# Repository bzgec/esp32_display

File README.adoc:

= MQTT display HW
:toc:
:sectnums:
:sectnumlevels: 4

* Current version: *0.1*
* link:./CHANGELOG.adoc[Changelog]

'''

MQTT display using:

* ESP32
* ILI9341 display

[link="./Res/pic/display_mqtt.jpg"]
.Example
image::./Res/pic/display_mqtt.jpg[alt="display_mqtt", height="250px", align="center"]

== PCB:

=== v0.1

[link="./Res/pic/hw_v0.1_bottom_real.jpg"]
.HW v0.1
image::./Res/pic/hw_v0.1_bottom_real.jpg[alt="hw_v0.1_bottom_real", height="300px", align="center"]

== Automated exporting
=== Installation
==== KiBot
link:https://github.com/INTI-CMNB/kibot#installation-using-pip[Installation]:

* `pip install --no-compile kibot`
(on Windows you probably need to install it in `KiCad Command Prompt`)

* On Arch Linux you can install it with: `paru -S kibot-git`
** You may need to install `pcbdraw-git` in case of
`module 'pcbnew' has no attribute 'PLOTTEXTMODE_STROKE'` error
(try to run `pcbnew --version` to be sure that program runs correctly)
** You also may need to install `imagemagick`: `sudo pacman -S imagemagick`
** You also may need to install few `pip` packages: `pip install mistune pybars3 wand`

==== recordmydesktop
* Needed only if running `kibot -vvv`
* Arch Linux: `sudo pacman -S recordmydesktop`

== TODO
* [ ] Fix silkscreen for programming connector (TX and RX are replaced, also the same for IO0 and RST)
* [ ] Remove Display module SD card slot - that way display can seat lower
  (whole PCB if then thinner)

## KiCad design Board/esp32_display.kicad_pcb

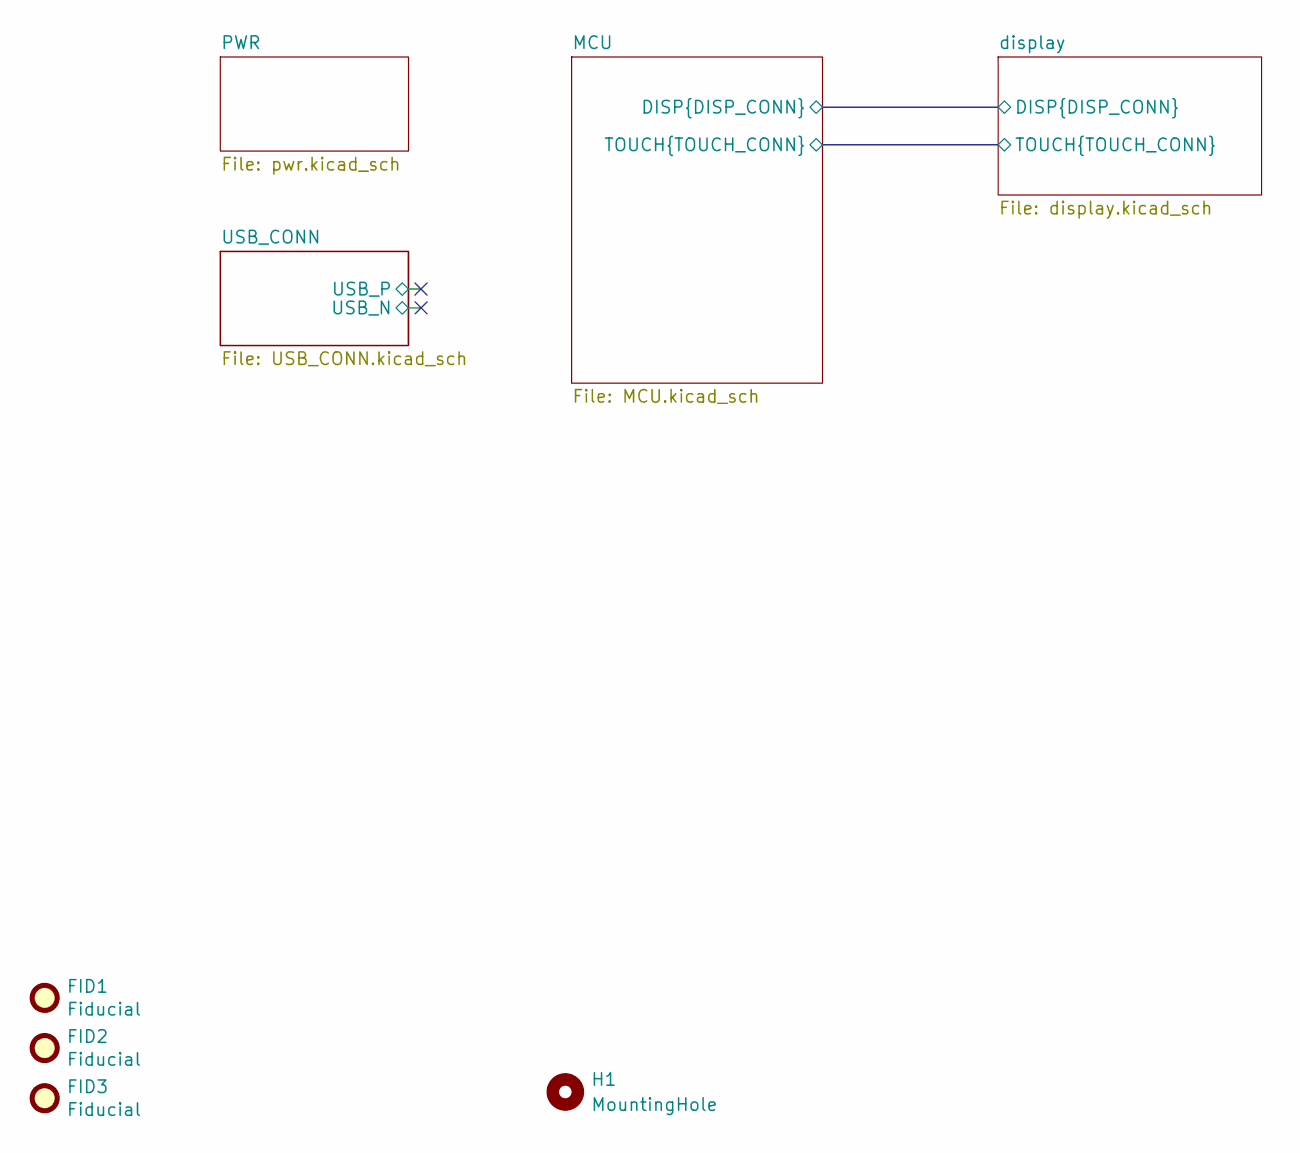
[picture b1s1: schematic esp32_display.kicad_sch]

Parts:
FID1, FID2, FID3: Fiducial; Fiducial_0.5mm_Mask1mm
H1: MountingHole; MountingHole_3.2mm_M3_ISO14580

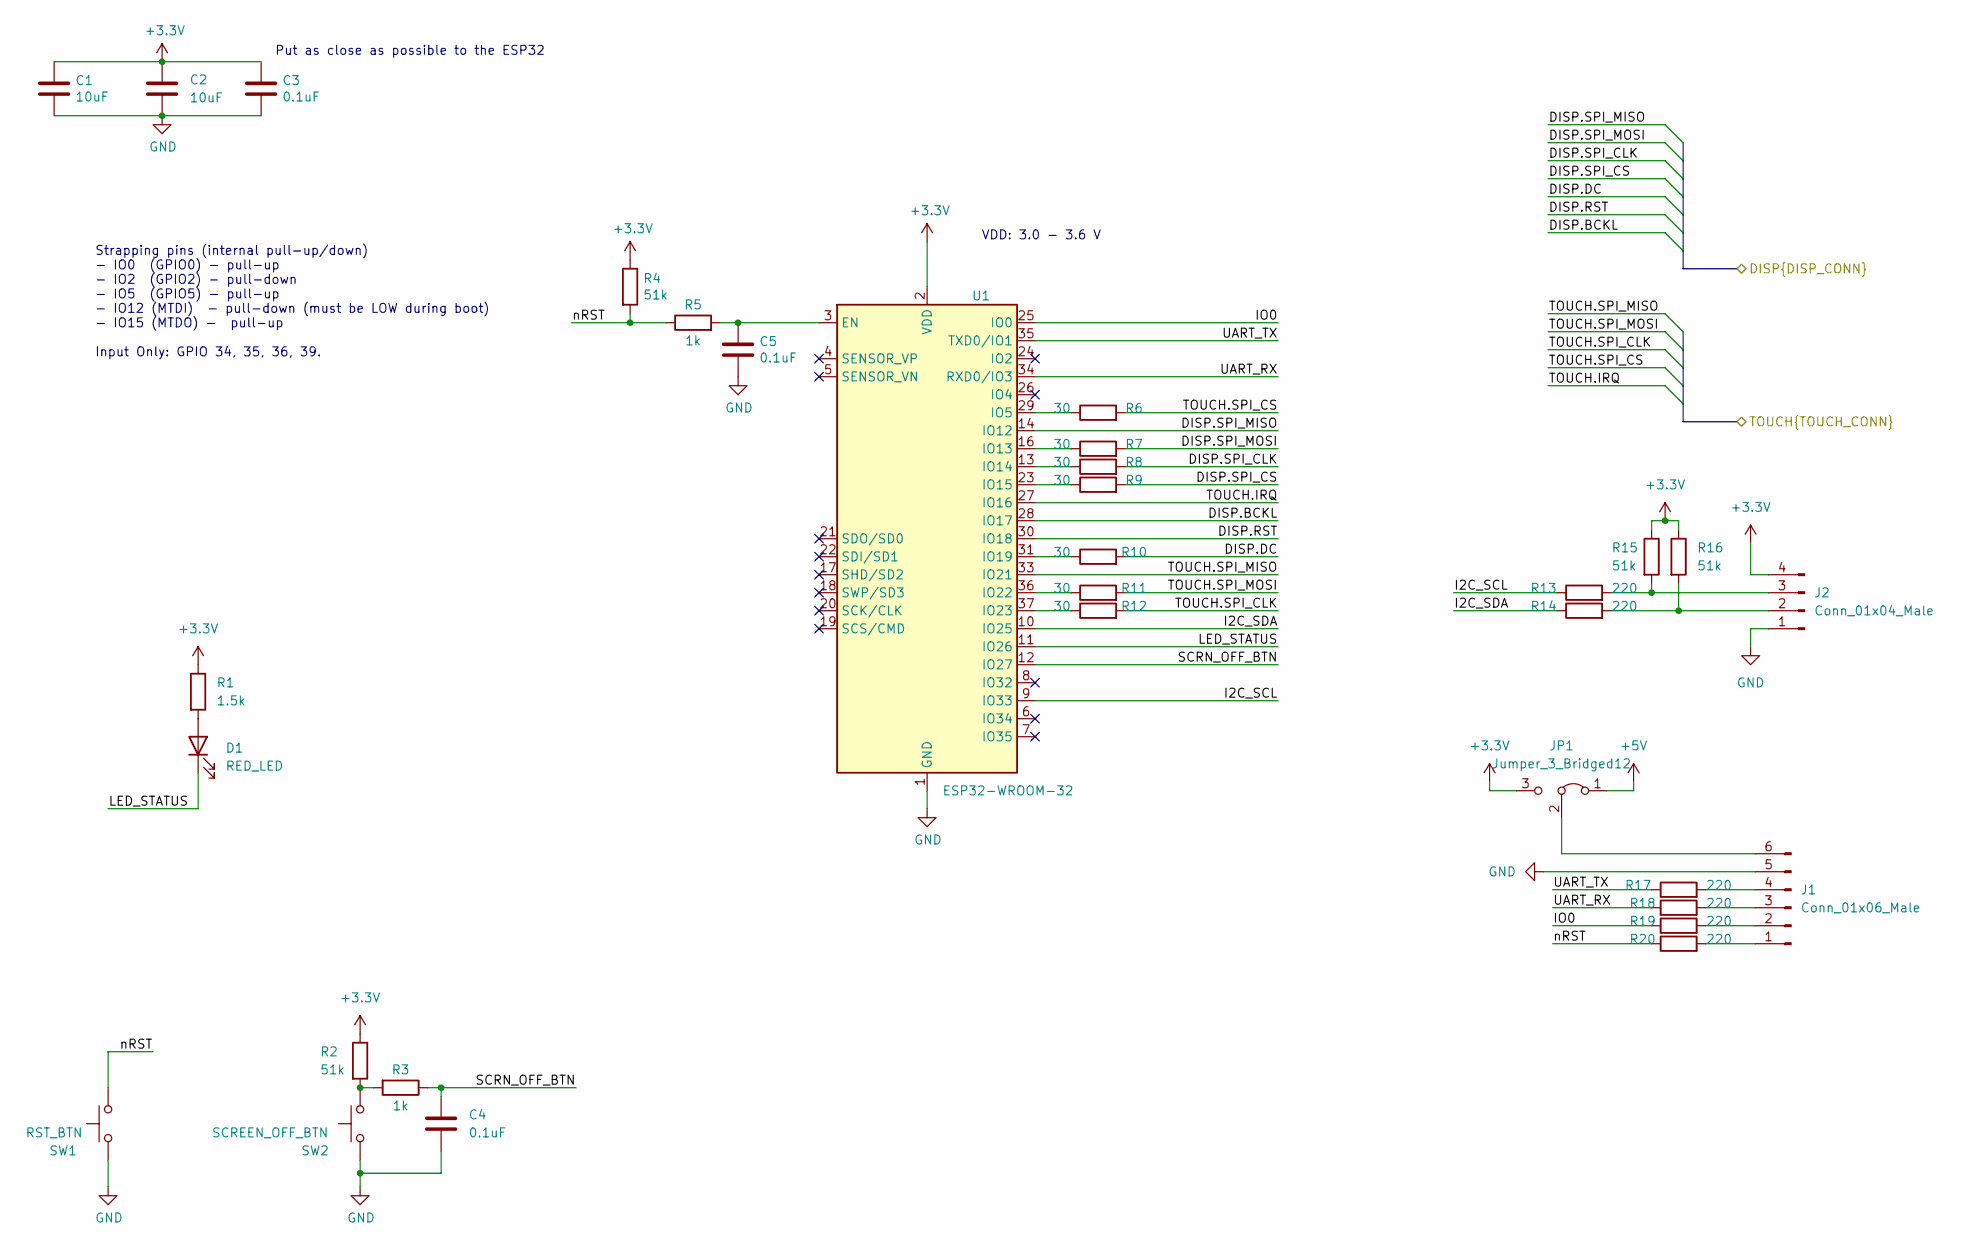
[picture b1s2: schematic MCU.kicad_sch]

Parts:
C1, C2: 10uF; C_0603_1608Metric_Pad1.08x0.95mm_HandSolder
C3, C4, C5: 0.1uF; C_0603_1608Metric_Pad1.08x0.95mm_HandSolder
D1: RED_LED; D_0603_1608Metric_Pad1.05x0.95mm_HandSolder
J1: Conn_01x06_Male; PinHeader_1x06_P2.54mm_Horizontal
J2: Conn_01x04_Male; PinHeader_1x04_P2.54mm_Horizontal
JP1: Jumper_3_Bridged12; SolderJumper-3_P1.3mm_Bridged12_RoundedPad1.0x1.5mm
R1: 1.5k; R_0603_1608Metric_Pad0.98x0.95mm_HandSolder
R2, R4, R15, R16: 51k; R_0603_1608Metric_Pad0.98x0.95mm_HandSolder
R3, R5: 1k; R_0603_1608Metric_Pad0.98x0.95mm_HandSolder
R6, R7, R8, R9, R10, R11, R12: 30; R_0603_1608Metric_Pad0.98x0.95mm_HandSolder
R13, R14, R17, R18, R19, R20: 220; R_0603_1608Metric_Pad0.98x0.95mm_HandSolder
SW1: RST_BTN; SW_Tactile_SPST_Angled_PTS645Vx83-2LFS
SW2: SCREEN_OFF_BTN; SW_Tactile_SPST_Angled_PTS645Vx83-2LFS
U1: ESP32-WROOM-32

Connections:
+3V3: C1.1, C2.1, C3.1, J2.4, JP1.3 (B), R1.1, R2.1, R4.1, R15.1, R16.1, U1.2 (VDD); also elsewhere on the board
+5V: JP1.1 (A); also elsewhere on the board
/MCU/DISP.BCKL: U1.28 (IO17); also elsewhere on the board
/MCU/DISP.DC: R10.2; also elsewhere on the board
/MCU/DISP.RST: U1.30 (IO18); also elsewhere on the board
/MCU/DISP.SPI_CLK: R8.2; also elsewhere on the board
/MCU/DISP.SPI_CS: R9.2; also elsewhere on the board
/MCU/DISP.SPI_MISO: U1.14 (IO12); also elsewhere on the board
/MCU/DISP.SPI_MOSI: R7.2; also elsewhere on the board
/MCU/I2C_SCL: R13.1, U1.9 (IO33)
/MCU/I2C_SDA: R14.1, U1.10 (IO25)
/MCU/IO0: R19.1, U1.25 (IO0)
/MCU/LED_STATUS: D1.1 (K), U1.11 (IO26)
/MCU/SCRN_OFF_BTN: C4.1, R3.1, U1.12 (IO27)
/MCU/TOUCH.IRQ: U1.27 (IO16); also elsewhere on the board
/MCU/TOUCH.SPI_CLK: R12.2; also elsewhere on the board
/MCU/TOUCH.SPI_CS: R6.2; also elsewhere on the board
/MCU/TOUCH.SPI_MISO: U1.33 (IO21); also elsewhere on the board
/MCU/TOUCH.SPI_MOSI: R11.2; also elsewhere on the board
/MCU/UART_RX: R18.1, U1.34 (RXD0/IO3)
/MCU/UART_TX: R17.1, U1.35 (TXD0/IO1)
/MCU/nRST: R4.2, R5.1, R20.1, SW1.1
GND: C1.2, C2.2, C3.2, C4.2, C5.2, J1.5, J2.1, SW1.2, SW2.2, U1.1 (GND), U1.15 (GND), U1.38 (GND), U1.39 (GND); also elsewhere on the board
unnamed: C5.1, R5.2, U1.3 (EN)
unnamed: D1.2 (A), R1.2
unnamed: J1.1, R20.2
unnamed: J1.2, R19.2
unnamed: J1.3, R18.2
unnamed: J1.4, R17.2
unnamed: J1.6, JP1.2 (C)
unnamed: J2.2, R14.2, R16.2
unnamed: J2.3, R13.2, R15.2
unnamed: R2.2, R3.2, SW2.1
unnamed: R6.1, U1.29 (IO5)
unnamed: R7.1, U1.16 (IO13)
unnamed: R8.1, U1.13 (IO14)
unnamed: R9.1, U1.23 (IO15)
unnamed: R10.1, U1.31 (IO19)
unnamed: R11.1, U1.36 (IO22)
unnamed: R12.1, U1.37 (IO23)

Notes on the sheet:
Put as close as possible to the ESP32
Strapping pins (internal pull-up/down) - IO0 (GPIO0) - pull-up - IO2 (GPIO2) - pull-down - IO5 (GPIO5) - pull-up - IO12 (MTDI) - pull-down (must be LOW during boot) - IO15 (MTDO) - pull-up Input Only: GPIO 34, 35, 36, 39.
VDD: 3.0 - 3.6 V

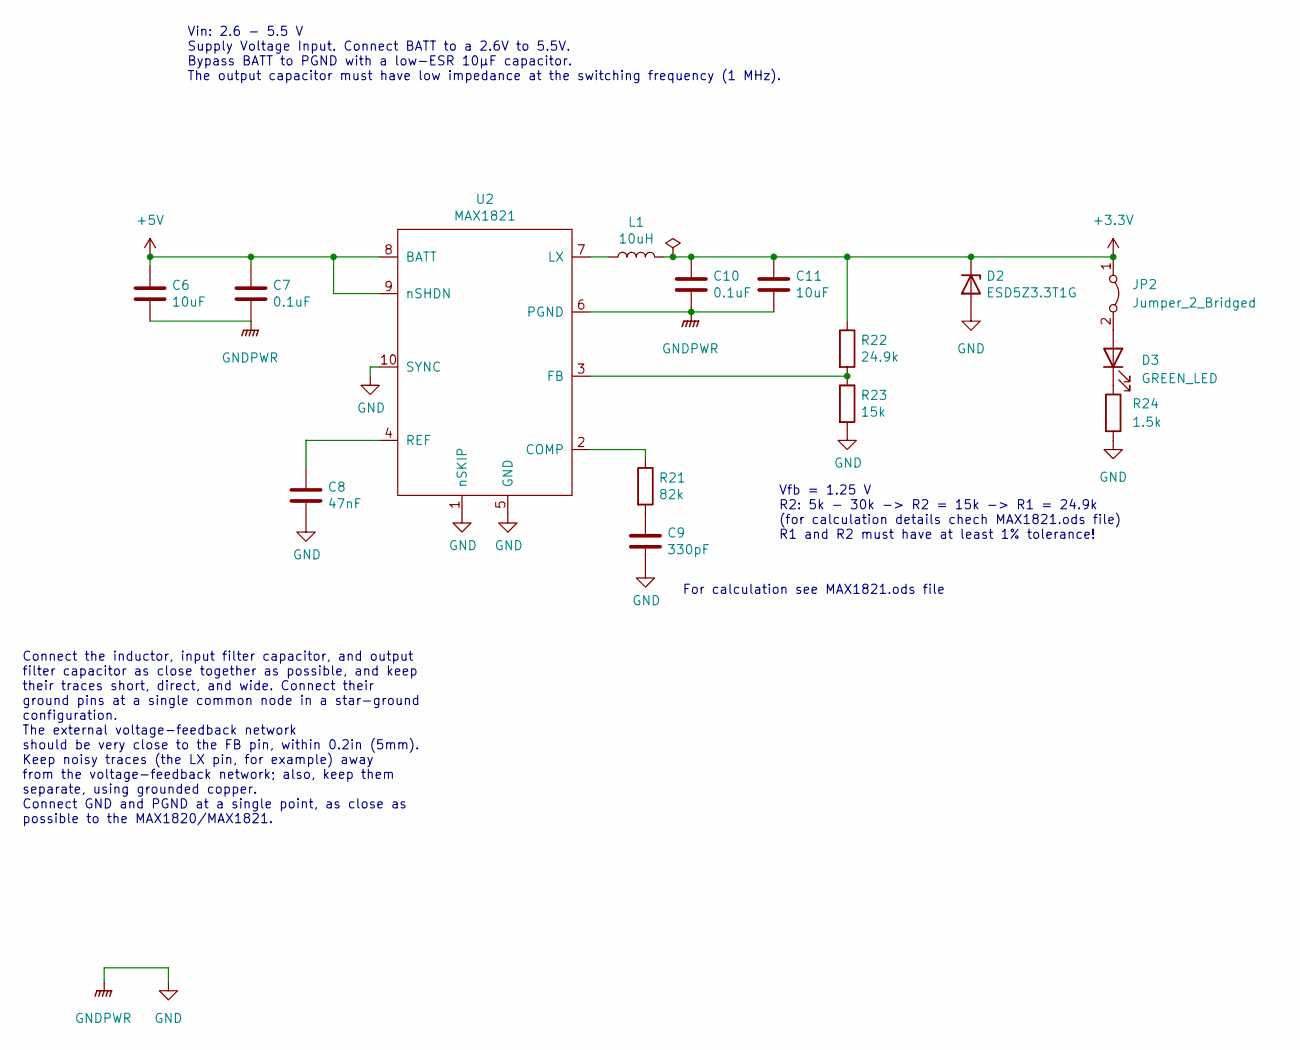
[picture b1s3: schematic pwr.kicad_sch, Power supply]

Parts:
C6, C11: 10uF; C_0603_1608Metric_Pad1.08x0.95mm_HandSolder
C7, C10: 0.1uF; C_0603_1608Metric_Pad1.08x0.95mm_HandSolder
C8: 47nF; C_0603_1608Metric_Pad1.08x0.95mm_HandSolder
C9: 330pF; C_0603_1608Metric_Pad1.08x0.95mm_HandSolder
D2: ESD5Z3.3T1G; D_SOD-523
D3: GREEN_LED; D_0603_1608Metric_Pad1.05x0.95mm_HandSolder
JP2: Jumper_2_Bridged; PinHeader_1x02_P2.54mm_Horizontal
L1: 10uH; NR6028T100M
R21: 82k; R_0603_1608Metric_Pad0.98x0.95mm_HandSolder
R22: 24.9k; R_0603_1608Metric_Pad0.98x0.95mm_HandSolder
R23: 15k; R_0603_1608Metric_Pad0.98x0.95mm_HandSolder
R24: 1.5k; R_0603_1608Metric_Pad0.98x0.95mm_HandSolder
U2: MAX1821; MAX1821EUB+

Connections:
+3V3: C10.1, C11.1, D2.1 (K), JP2.1 (A), L1.2, R22.1; also elsewhere on the board
+5V: C6.1, C7.1, U2.8 (BATT), U2.9 (nSHDN); also elsewhere on the board
GND: C6.2, C7.2, C8.2, C9.2, C10.2, C11.2, D2.2 (A), R23.2, R24.2, U2.1 (nSKIP), U2.5 (GND), U2.6 (PGND), U2.10 (SYNC); also elsewhere on the board
unnamed: C8.1, U2.4 (REF)
unnamed: C9.1, R21.2
unnamed: D3.1 (K), R24.1
unnamed: D3.2 (A), JP2.2 (B)
unnamed: L1.1, U2.7 (LX)
unnamed: R21.1, U2.2 (COMP)
unnamed: R22.2, R23.1, U2.3 (FB)

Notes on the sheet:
Vfb = 1.25 V R2: 5k - 30k -> R2 = 15k -> R1 = 24.9k (for calculation details chech MAX1821.ods file) R1 and R2 must have at least 1% tolerance!
For calculation see MAX1821.ods file
Connect the inductor, input filter capacitor, and output filter capacitor as close together as possible, and keep their traces short, direct, and wide. Connect their ground pins at a single common node in a star-ground configuration. The external voltage-feedback network should be very close to the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
Vin: 2.6 - 5.5 V Supply Voltage Input. Connect BATT to a 2.6V to 5.5V. Bypass BATT to PGND with a low-ESR 10μF capacitor. The output capacitor must have low impedance at the switching frequency (1 MHz).

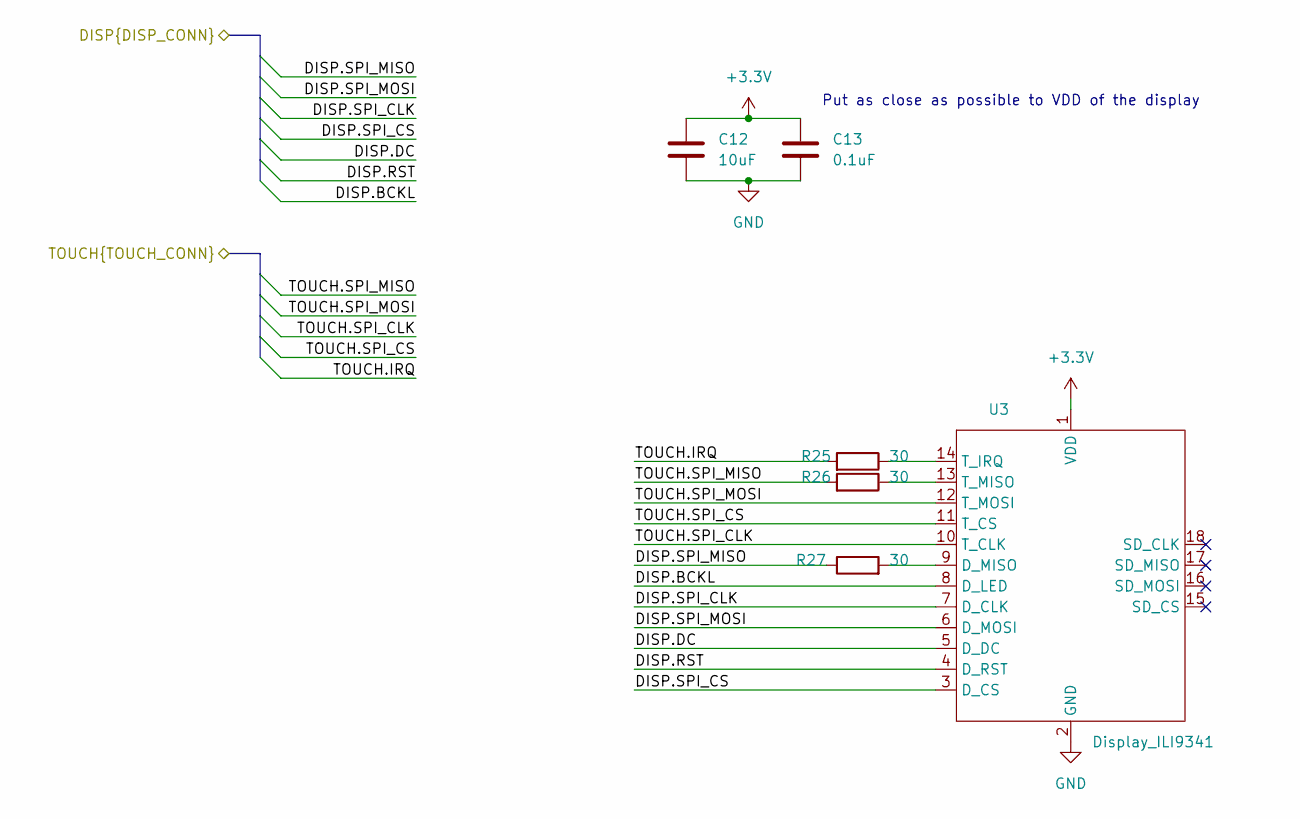
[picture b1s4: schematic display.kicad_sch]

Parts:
C12: 10uF; C_0603_1608Metric_Pad1.08x0.95mm_HandSolder
C13: 0.1uF; C_0603_1608Metric_Pad1.08x0.95mm_HandSolder
R25, R26, R27: 30; R_0603_1608Metric_Pad0.98x0.95mm_HandSolder
U3: Display_ILI9341; ILI9341

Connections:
+3V3: C12.1, C13.1, U3.1 (VDD); also elsewhere on the board
/MCU/DISP.BCKL: U3.8 (D_LED); also elsewhere on the board
/MCU/DISP.DC: U3.5 (D_DC); also elsewhere on the board
/MCU/DISP.RST: U3.4 (D_RST); also elsewhere on the board
/MCU/DISP.SPI_CLK: U3.7 (D_CLK); also elsewhere on the board
/MCU/DISP.SPI_CS: U3.3 (D_CS); also elsewhere on the board
/MCU/DISP.SPI_MISO: R27.1; also elsewhere on the board
/MCU/DISP.SPI_MOSI: U3.6 (D_MOSI); also elsewhere on the board
/MCU/TOUCH.IRQ: R25.2; also elsewhere on the board
/MCU/TOUCH.SPI_CLK: U3.10 (T_CLK); also elsewhere on the board
/MCU/TOUCH.SPI_CS: U3.11 (T_CS); also elsewhere on the board
/MCU/TOUCH.SPI_MISO: R26.2; also elsewhere on the board
/MCU/TOUCH.SPI_MOSI: U3.12 (T_MOSI); also elsewhere on the board
GND: C12.2, C13.2, U3.2 (GND); also elsewhere on the board
unnamed: R25.1, U3.14 (T_IRQ)
unnamed: R26.1, U3.13 (T_MISO)
unnamed: R27.2, U3.9 (D_MISO)

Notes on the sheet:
Put as close as possible to VDD of the display

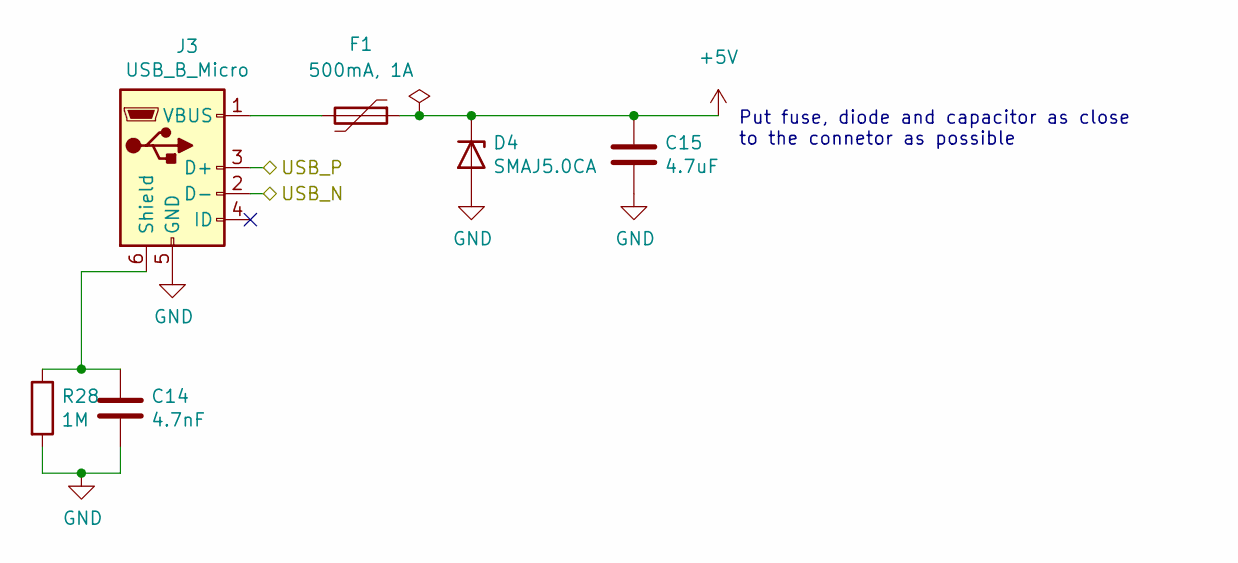
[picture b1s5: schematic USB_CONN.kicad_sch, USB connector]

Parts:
C14: 4.7nF; C_0603_1608Metric_Pad1.08x0.95mm_HandSolder
C15: 4.7uF; C_0603_1608Metric_Pad1.08x0.95mm_HandSolder
D4: SMAJ5.0CA; D_SMA
F1: 500mA, 1A; Fuse_1206_3216Metric_Pad1.42x1.75mm_HandSolder
J3: USB_B_Micro; USB_Micro-B_Molex-105017-0001
R28: 1M; R_0603_1608Metric_Pad0.98x0.95mm_HandSolder

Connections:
+5V: C15.1, D4.1 (K), F1.1; also elsewhere on the board
/USB_CONN/USB_N: J3.2 (D-)
/USB_CONN/USB_P: J3.3 (D+)
GND: C14.2, C15.2, D4.2 (A), J3.5 (GND), R28.2; also elsewhere on the board
unnamed: C14.1, J3.6 (Shield), R28.1
unnamed: F1.2, J3.1 (VBUS)

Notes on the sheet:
Put fuse, diode and capacitor as close to the connetor as possible

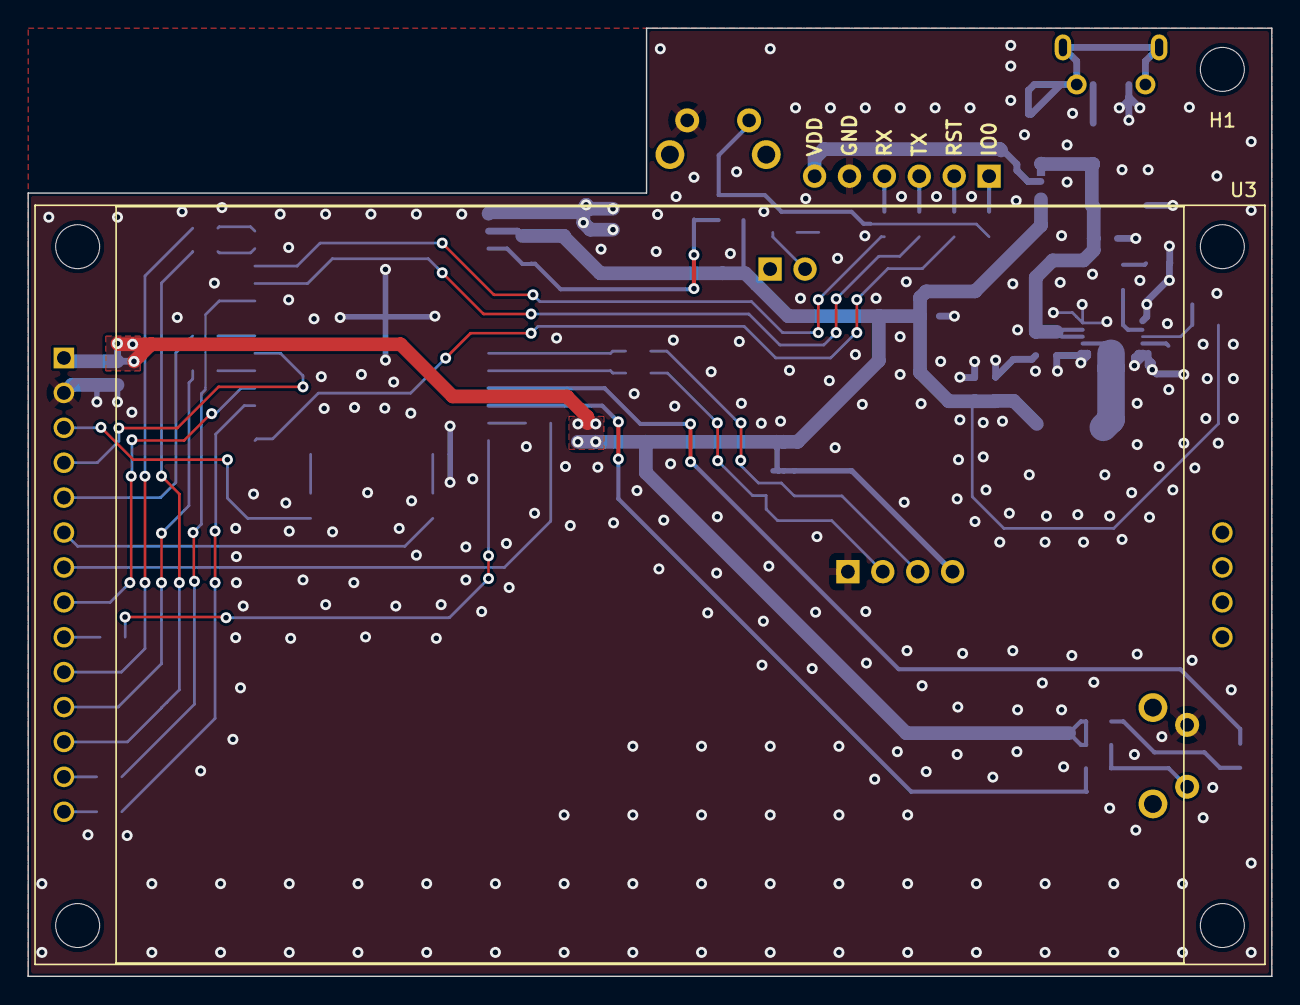
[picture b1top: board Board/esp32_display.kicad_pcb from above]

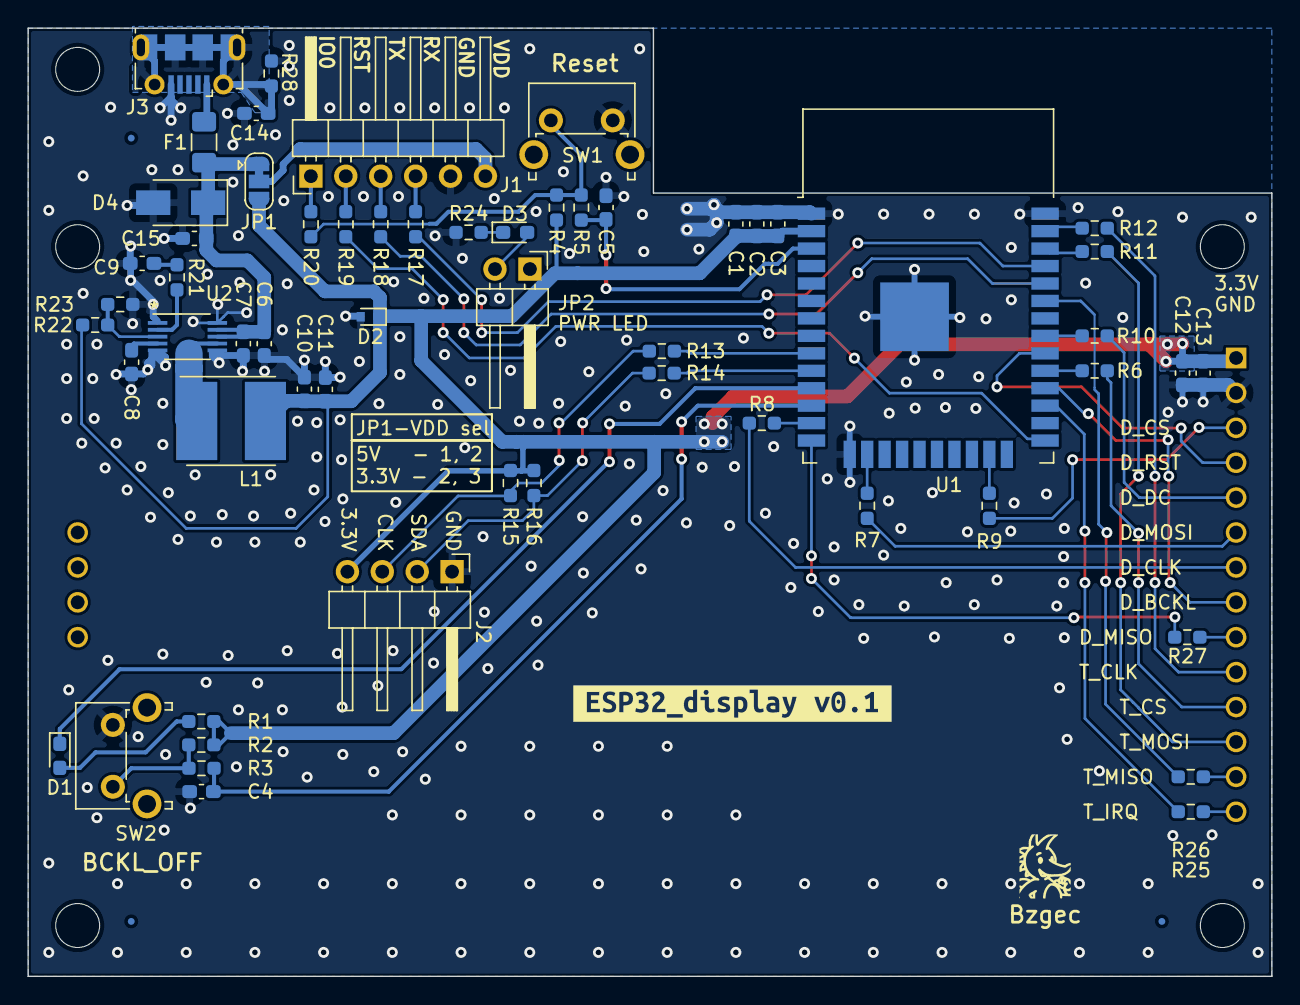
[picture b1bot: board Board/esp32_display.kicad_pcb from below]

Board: 2 copper layers, 90.5 x 69.0 mm, 64 parts (62 on the bottom side), 52 nets.

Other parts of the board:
kibuzzard-61D6E91A: G***; kibuzzard-61D6E91A

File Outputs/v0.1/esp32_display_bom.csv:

Row,Description,Part,References,Value,Footprint,Quantity Per PCB,Status,Datasheet
1,Unpolarized capacitor,C,C9,330pF,C_0603_1608Metric_Pad1.08x0.95mm_HandSolder,1, ,~
2,Unpolarized capacitor,C,C14,4.7nF,C_0603_1608Metric_Pad1.08x0.95mm_HandSolder,1, ,~
3,Unpolarized capacitor,C,C8,47nF,C_0603_1608Metric_Pad1.08x0.95mm_HandSolder,1, ,~
4,Unpolarized capacitor,C,C3-C5 C7 C10 C13,0.1uF,C_0603_1608Metric_Pad1.08x0.95mm_HandSolder,6, ,~
5,Unpolarized capacitor,C,C15,4.7uF,C_0603_1608Metric_Pad1.08x0.95mm_HandSolder,1, ,~
6,Unpolarized capacitor,C,C1 C2 C6 C11 C12,10uF,C_0603_1608Metric_Pad1.08x0.95mm_HandSolder,5, ,~
7,Zener diode,D_Zener,D2,ESD5Z3.3T1G,D_SOD-523,1, ,https://www.onsemi.com/pdf/datasheet/esd5z2.5t1-d.pdf
8,Light emitting diode,LED,D3,GREEN_LED,D_0603_1608Metric_Pad1.05x0.95mm_HandSolder,1, ,~
9,Light emitting diode,LED,D1,RED_LED,D_0603_1608Metric_Pad1.05x0.95mm_HandSolder,1, ,https://www.we-online.com/katalog/datasheet/150060RS75000.pdf
10,Zener diode,D_Zener,D4,SMAJ5.0CA,D_SMA,1, ,https://www.littelfuse.com/~/media/electronics/datasheets/tv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
11,"Resettable fuse, polymeric positive temperature coefficient",Polyfuse,F1,"500mA, 1A",Fuse_1206_3216Metric_Pad1.42x1.75mm_HandSolder,1, ,http://www.littelfuse.com/data/en/Data_Sheets/Littelfuse_PTC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
12,"Generic connector, single row, 01x06, script generated (kicad-library-utils/schlib/autogen/connector/)",Conn_01x06_Male,J1,Conn_01x06_Male,PinHeader_1x06_P2.54mm_Horizontal,1, ,~
13,USB Micro Type B connector,USB_B_Micro,J2,USB_B_Micro,USB_Micro-B_Molex-105017-0001,1, ,https://cdn.amphenol-icc.com/media/wysiwyg/files/drawing/101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
14,"Jumper, 3-pole, pins 1+2 closed/bridged",Jumper_3_Bridged12,JP1,Jumper_3_Bridged12,SolderJumper-3_P1.3mm_Bridged12_RoundedPad1.0x1.5mm,1, ,~
15,Inductor,L,L1,10uF,NR6028T100M,1, ,~
16,Resistor,R,R6-R12 R21-R23,30,R_0603_1608Metric_Pad0.98x0.95mm_HandSolder,10, ,~
17,Resistor,R,R13-R16,220,R_0603_1608Metric_Pad0.98x0.95mm_HandSolder,4, ,~
18,Resistor,R,R3 R5,1k,R_0603_1608Metric_Pad0.98x0.95mm_HandSolder,2, ,~
19,Resistor,R,R1 R20,1.5k,R_0603_1608Metric_Pad0.98x0.95mm_HandSolder,2, ,~
20,Resistor,R,R19,15k,R_0603_1608Metric_Pad0.98x0.95mm_HandSolder,1, ,~
21,Resistor,R,R18,24.9k,R_0603_1608Metric_Pad0.98x0.95mm_HandSolder,1, ,~
22,Resistor,R,R2 R4,51k,R_0603_1608Metric_Pad0.98x0.95mm_HandSolder,2, ,~
23,Resistor,R,R17,82k,R_0603_1608Metric_Pad0.98x0.95mm_HandSolder,1, ,~
24,Resistor,R,R24,1M,R_0603_1608Metric_Pad0.98x0.95mm_HandSolder,1, ,~
25,"Push button switch, generic, two pins",SW_Push,SW1,RST_BTN,SW_Tactile_SPST_Angled_PTS645Vx83-2LFS,1, ,~
26,"Push button switch, generic, two pins",SW_Push,SW2,SCREEN_OFF_BTN,SW_Tactile_SPST_Angled_PTS645Vx83-2LFS,1, ,~
27,"3.2"" TFT, 240x320, 3.3V logic, 3.3V/5V power",Display_ILI9341,U3,Display_ILI9341,ILI9341,1, ,
28,"RF Module, ESP32-D0WDQ6 SoC, Wi-Fi 802.11b/g/n, Bluetooth, BLE, 32-bit, 2.7-3.6V, onboard antenna, SMD",ESP32-WROOM-32,U1,ESP32-WROOM-32,ESP32-WROOM-32,1, ,https://www.espressif.com/sites/default/files/documentation/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
29,,MAX1821,U2,MAX1821,MAX1821EUB+,1, ,https://datasheets.maximintegrated.com/en/ds/MAX1820-MAX1821X.pdf





Project info:
Schematic:,esp32_display
Variant:,default
Revision:,v0.1
Date:,2022/01/07
KiCad Version:,6.0.0
Statistics:
Component Groups:,29
Component Count:,53
Fitted Components:,53
Number of PCBs:,1
Total Components:,53

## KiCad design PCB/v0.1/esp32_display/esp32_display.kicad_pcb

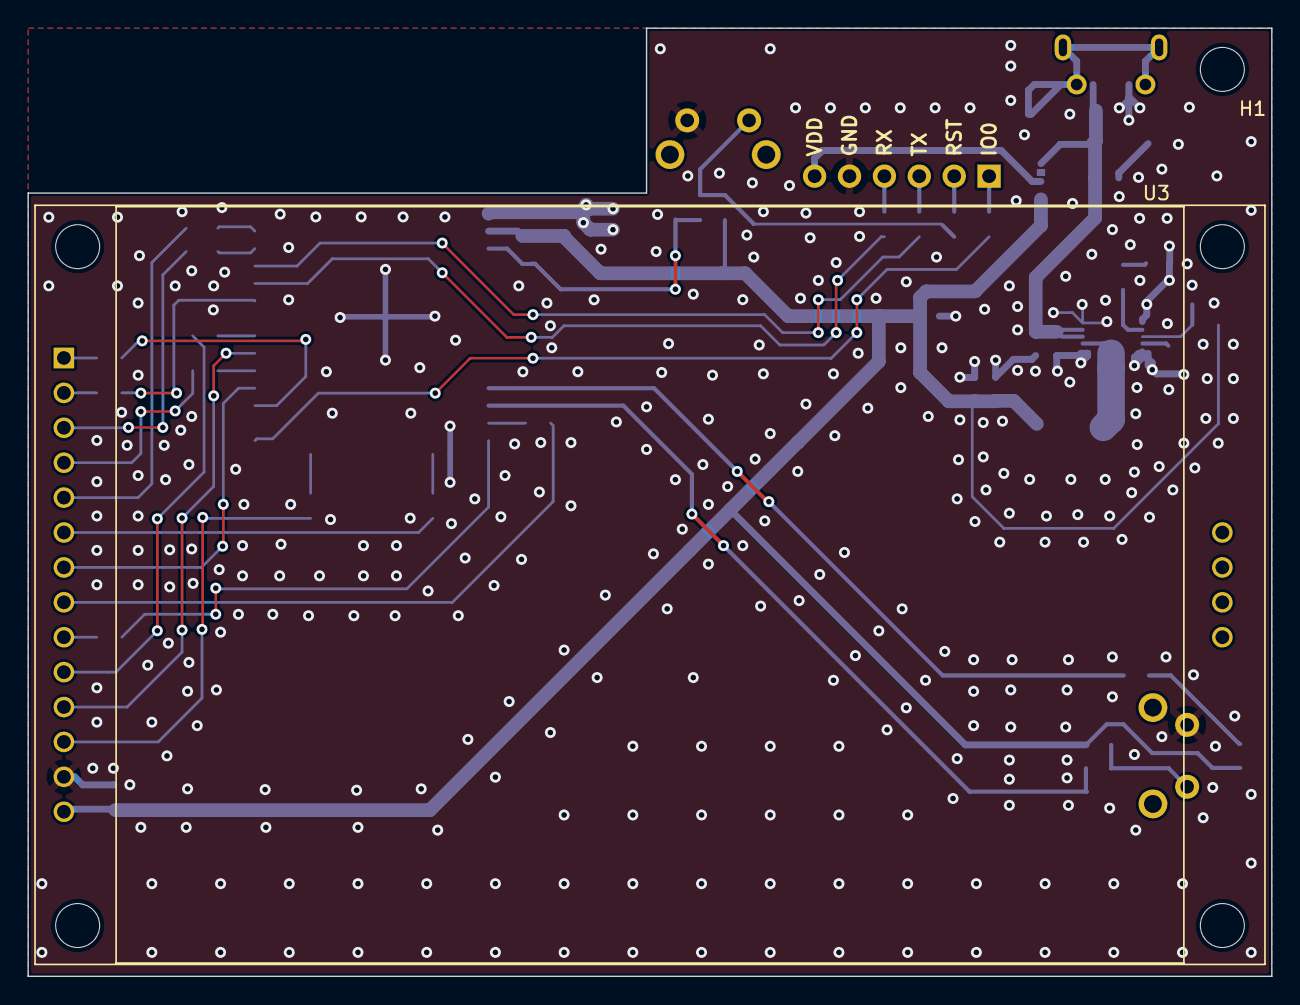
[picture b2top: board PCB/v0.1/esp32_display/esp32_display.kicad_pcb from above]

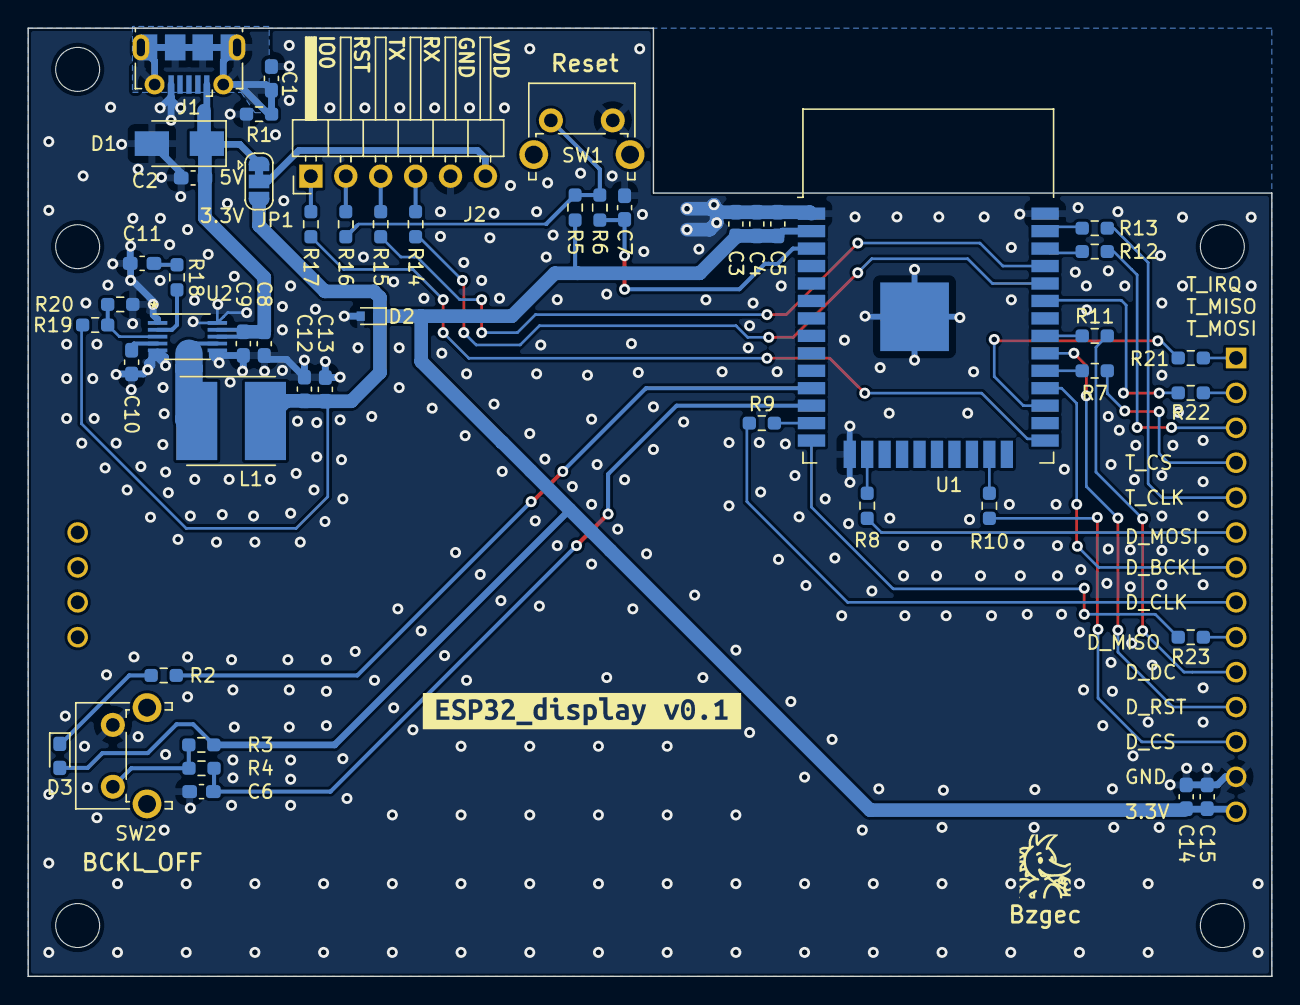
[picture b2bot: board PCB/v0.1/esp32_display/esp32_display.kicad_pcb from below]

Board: 2 copper layers, 90.5 x 69.0 mm, 52 parts (50 on the bottom side), 45 nets.

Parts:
C1: 4.7nF; C_0603_1608Metric_Pad1.08x0.95mm_HandSolder
C2: 4.7uF; C_0603_1608Metric_Pad1.08x0.95mm_HandSolder
C3, C4, C8, C13, C14: 10uF; C_0603_1608Metric_Pad1.08x0.95mm_HandSolder
C5, C6, C7, C9, C12, C15: 0.1uF; C_0603_1608Metric_Pad1.08x0.95mm_HandSolder
C10: 47nF; C_0603_1608Metric_Pad1.08x0.95mm_HandSolder
C11: 330pF; C_0603_1608Metric_Pad1.08x0.95mm_HandSolder
D1: SMAJ5.0CA; D_SMA
D2: ESD5Z3.3T1G; D_SOD-523
D3: LED; D_0603_1608Metric_Pad1.05x0.95mm_HandSolder
H1: MountingHole_Pad; MountingHole_3.2mm_M3_ISO14580
J1: USB_B_Micro; USB_Micro-B_Molex-105017-0001
J2: Conn_01x06_Male; PinHeader_1x06_P2.54mm_Horizontal
JP1: Jumper_3_Bridged12; SolderJumper-3_P1.3mm_Bridged12_RoundedPad1.0x1.5mm
L1: 10uF; NR6028T100M
R1: 1M; R_0603_1608Metric_Pad0.98x0.95mm_HandSolder
R2: 1.5k; R_0603_1608Metric_Pad0.98x0.95mm_HandSolder
R3, R5: 51k; R_0603_1608Metric_Pad0.98x0.95mm_HandSolder
R4, R6: 1k; R_0603_1608Metric_Pad0.98x0.95mm_HandSolder
R7, R8, R9, R10, R11, R12, R13, R21, R22, R23: 30; R_0603_1608Metric_Pad0.98x0.95mm_HandSolder
R14, R15, R16, R17: 220; R_0603_1608Metric_Pad0.98x0.95mm_HandSolder
R18: 82k; R_0603_1608Metric_Pad0.98x0.95mm_HandSolder
R19: 24.9k; R_0603_1608Metric_Pad0.98x0.95mm_HandSolder
R20: 15k; R_0603_1608Metric_Pad0.98x0.95mm_HandSolder
SW1: RST_BTN; SW_Tactile_SPST_Angled_PTS645Vx83-2LFS
SW2: SCREEN_OFF_BTN; SW_Tactile_SPST_Angled_PTS645Vx83-2LFS
U1: ESP32-WROOM-32
U2: MAX1821; MAX1821EUB+
U3: Display_ILI9341; ILI9341
kibuzzard-61D6E91A: G***; kibuzzard-61D6E91A

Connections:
+3V3: C3.1, C4.1, C5.1, C12.1, C13.1, C14.1, C15.1, D2.1 (K), D3.2 (A), JP1.3 (B), L1.2, R3.1, R5.1, R19.1, U1.2 (VDD), U3.14 (VDD)
+5V: C2.1, C8.1, C9.1, D1.1 (K), J1.1 (VBUS), JP1.1 (A), U2.8 (BATT), U2.9 (nSHDN)
/MCU/DISP.BCKL: U1.28 (IO17), U3.7 (D_LED)
/MCU/DISP.DC: R11.2, U3.10 (D_DC)
/MCU/DISP.RST: U1.30 (IO18), U3.11 (D_RST)
/MCU/DISP.SPI_CLK: R9.2, U3.8 (D_CLK)
/MCU/DISP.SPI_CS: R10.2, U3.12 (D_CS)
/MCU/DISP.SPI_MISO: R23.2, U1.14 (IO12)
/MCU/DISP.SPI_MOSI: R8.2, U3.6 (D_MISO)
/MCU/IO0: R17.1, U1.25 (IO0)
/MCU/LED_STATUS: R2.2, U1.11 (IO26)
/MCU/RST: R5.2, R6.1, R16.1, SW1.1
/MCU/SCRN_OFF_BTN: C6.1, R4.1, U1.12 (IO27)
/MCU/TOUCH.IRQ: R21.2, U1.27 (IO16)
/MCU/TOUCH.SPI_CLK: R13.2, U3.5 (T_CLK)
/MCU/TOUCH.SPI_CS: R7.2, U3.4 (T_CS)
/MCU/TOUCH.SPI_MISO: R22.2, U1.33 (IO21)
/MCU/TOUCH.SPI_MOSI: R12.2, U3.3 (T_MOSI)
/MCU/UART_RX: R14.1, U1.34 (RXD0/IO3)
/MCU/UART_TX: R15.1, U1.35 (TXD0/IO1)
GND: C1.2, C2.2, C3.2, C4.2, C5.2, C6.2, C7.2, C8.2, C9.2, C10.2, C11.2, C12.2, C13.2, C14.2, C15.2, D1.2 (A), D2.2 (A), J1.5 (GND), J2.5, R1.2, R20.2, SW1.2, SW2.2, U1.1 (GND), U1.15 (GND), U1.38 (GND), U1.39 (GND), U2.1 (nSKIP), U2.5 (GND), U2.6 (PGND), U2.10 (SYNC), U3.13 (GND)
unnamed: C1.1, J1.6 (Shield), R1.1
unnamed: C7.1, R6.2, U1.3 (EN)
unnamed: C10.1, U2.4 (REF)
unnamed: C11.1, R18.2
unnamed: D3.1 (K), R2.1
unnamed: J2.1, R17.2
unnamed: J2.2, R16.2
unnamed: J2.3, R15.2
unnamed: J2.4, R14.2
unnamed: J2.6, JP1.2 (C)
unnamed: L1.1, U2.7 (LX)
unnamed: R3.2, R4.2, SW2.1
unnamed: R7.1, U1.29 (IO5)
unnamed: R8.1, U1.16 (IO13)
unnamed: R9.1, U1.13 (IO14)
unnamed: R10.1, U1.23 (IO15)
unnamed: R11.1, U1.31 (IO19)
unnamed: R12.1, U1.36 (IO22)
unnamed: R13.1, U1.37 (IO23)
unnamed: R18.1, U2.2 (COMP)
unnamed: R19.2, R20.1, U2.3 (FB)
unnamed: R21.1, U3.1 (T_IRQ)
unnamed: R22.1, U3.2 (T_MISO)
unnamed: R23.1, U3.9 (D_MOSI)

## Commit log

2021-12-30 Add housing edge, generate output files
2022-01-03 Smaller footprint, no housing, right angle buttons
2022-01-04 Add serial resistors to SPI lines (PCB not finished)
    Still missing placment of RC filters.
2022-01-04 Rename TVS/ESD protection diodes to their name (5V and 3.3V)
2022-01-04 Add square around PCB name and verion
2022-01-05 Place RC filters (close to buttons)
2022-01-05 Dont route L of buck converter through vias
2022-01-05 Fix 3d models, generate outputs, add .wrl to outputs
2022-01-06 Fix myLib footprint path (from absolute to relative)
2022-01-06 Buck converter feedback line on top
    PCB name and version generated with KiBuzzard
2022-01-06 Move from PCB/v0.1/esp32_display to Board/v0.1
2022-01-06 Fix board -> Board
2022-01-06 Clean schematics (add date and revision...)
2022-01-06 Move ".kibot.yaml" to Board... folder
2022-01-07 Add polyfuse, 3.3V status LED, USB_CONN sheet
2022-01-07 Fix missing pad for H1, fix missing power input ERC error
    ERC error was: Input power pin not driven by any output power pins.
    Fix was adding PWR_FLAG power symbol after polyfuse or inductor.
2022-01-07 Add KiBot DRC filters
2022-01-07 Generate gerbers, sch and BOM with KiBot
2022-01-07 Fix .gitignore
2022-01-07 Try to implement pcbdraw
2022-01-07 Working pcbdraw - generating *_pcbdraw_*.jpg
2022-01-07 Try to implement .step export
2022-01-08 Fix some via position, chane Net-(J1-Pad6) trace width
2022-01-09 Add ILI9341 3D model, change few via positions
2022-01-09 Fix ILI9341 display symbol (pin numbering)
2022-01-10 Add jumper for 3.3V power LED
2022-01-10 Add info about ESP32 strapping pins
2022-01-10 Add labels to unused pins
2022-01-11 Relative myLib path
2022-01-12 Fix path for manual exporting of .step and .wrl
2022-01-12 Move Board/v0.1 to Board, move kicadLib to Board/kicadLib, remove Outputs
2022-01-14 Add I2C pin header
2022-01-14 KiBot .step export - substitute STEP in place of VRML
2022-01-17 Fix USB silkscreen over board warning, other minimal fixes
2022-01-18 Add fiducials
2022-01-18 Add pdf_pcb_print to .kibot.yaml
2022-01-18 Add dpi option for pcbdraw in .kibot.yaml
2022-01-19 Add Paste layer to JLCPCB gerber config
2022-01-20 Fix buck inductor (uF -> uH)
2022-02-05 Update README (TODO)
2022-09-10 Update typo

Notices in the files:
parts and their libraries:
Copyright 2021 Accelerated Designs. All rights reserved.
